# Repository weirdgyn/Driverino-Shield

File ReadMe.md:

# Driverino-Shield

### (italian noun) /ˈdraɪvərnəʊ/ : *little driver*

Driverino-Shield is a simple, low power, controller for [BLDC](https://en.wikipedia.org/wiki/Brushless_DC_electric_motor) sensored motors.
The aim of the project was to create an Arduino shield to drive PM BLDC motor(s) rated about 50-100W.
The board is designed around TI MCT8316Z BLDC chip: a very compact full featured driver that can be easily controlled from Arduino microcontroller.

PCB has been fully designed with KiCAD.

# TODO:

- [X] Submit to Made-With-KiCAD
- [ ] Add features:
   - [ ] encoder input.
   - [ ] current measurement (via INA250).
- [ ] Optimize PCB layout.
- [ ] Write Library.
   - [ ] Write Firmware.

# License

This project is released under CERN Open Hardware Licence Version 2 - Permissive.

# Links
* [This project on kitspace](https://kitspace.org/boards/github.com/weirdgyn/driverino-shield/)
* [TI MCT8316Z](https://www.ti.com/product/MCT8316Z?keyMatch=MCT8316Z&tisearch=search-everything)
* [Arduino](https://www.arduino.cc/)
* [KiCAD](https://www.kicad.org/)

#

Live long and prosper!

That's all folks.

By[t]e{s} Weirdgyn

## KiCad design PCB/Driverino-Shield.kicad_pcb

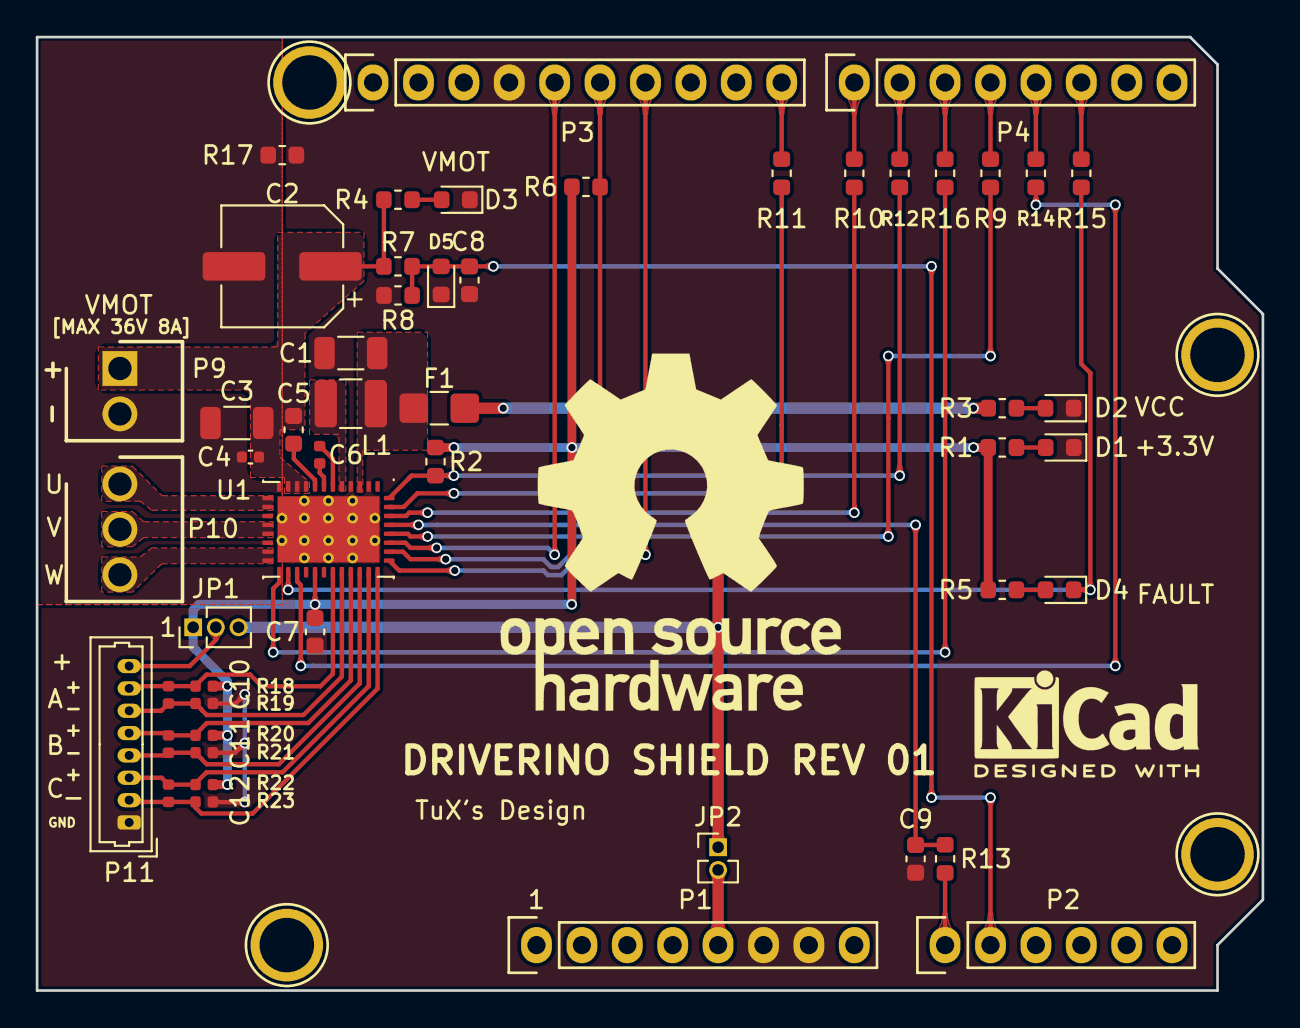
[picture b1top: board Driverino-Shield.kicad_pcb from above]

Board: 2 copper layers, 68.6 x 53.3 mm, 56 parts (0 on the bottom side), 47 nets.

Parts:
C1: 22uF; C_1206_3216Metric
C2: 150uF; CP_Elec_6.3x7.7
C3: 10uF; C_1206_3216Metric
C4, C10, C11, C12: 100nF; C_0402_1005Metric
C5, C7: 1uF; C_0603_1608Metric
C6: 10nF; C_0402_1005Metric
C8, C9: 100nF; C_0603_1608Metric
D1: ORANGE; LED_0603_1608Metric
D2, D4: BLUE; LED_0603_1608Metric
D3: GREEN; LED_0603_1608Metric
D5: Vz=5V; D_0603_1608Metric
F1: 200mA; Fuse_1206_3216Metric_Castellated
JP1: HAL_SEL; PinHeader_1x03_P1.27mm_Vertical
JP2: VCC_SEL; PinHeader_1x02_P1.27mm_Vertical
L1: 47uH; L_1210_3225Metric
P1: Power; Socket_Strip_Arduino_1x08
P2: Analog; Socket_Strip_Arduino_1x06
P3: Digital; Socket_Strip_Arduino_1x10
P4: Digital; Socket_Strip_Arduino_1x08
P5, P6, P7, P8: CONN_01X01; Arduino_1pin
P9: PWR; 39773-0002
P10: MOT; 39773-0003
P11: HALL; Molex_PicoBlade_53047-0810_1x08_P1.25mm_Vertical
R1, R3, R5, R7, R8, R13: 1k; R_0603_1608Metric
R2, R6: 5.1k; R_0603_1608Metric
R4: 4.7k; R_0603_1608Metric
R9, R10, R11, R12, R14, R15, R16, R17: 0R; R_0603_1608Metric
R18, R20, R22: 10k; R_0402_1005Metric
R19, R21, R23: 0R; R_0402_1005Metric
U1: MCT8316Z; QFN-40_EP_5x7_Pitch0.5mm

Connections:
+3.3V: C7.1, JP1.1, P1.4, R1.1, R2.1, R5.1, R6.1, R18.2, R20.2, R22.2, U1.25
+5V: JP2.2, P1.5
+36V: C2.1, C3.2, C4.2, C5.2, P9.1, R4.1, R7.2, U1.9, U1.10, U1.11
/2: P4.6, R15.1
/3(**): P4.5, R14.1
/4: P4.4, R9.1
/5(**): P4.3, R16.1
/6(**): P4.2, R12.1
/7: P4.1, R10.1
/8: P3.10, R11.1
/11(**/MOSI): P3.7, U1.34
/12(MISO): P3.6, R6.2, U1.33
/13(SCK): P3.5, U1.35
/A0: P2.1, R13.2
/A1: C8.2, D5.2, P2.2, R7.1, R8.1
/A4(SDA): P2.5, P3.2
/A5(SCL): P2.6, P3.1
/BRAKE: R10.2, U1.38
/CS: R9.2, U1.36
/DRVOFF: R16.2, U1.21
/FAULT: D4.1, R15.2, U1.22
/FB: C1.2, F1.2, L1.1, U1.3
/FGOUT: R2.2, R12.2, U1.40
/HAN: C10.1, P11.6, R19.1, U1.28
/HAP: C10.2, P11.7, R18.1, U1.27
/HBN: C11.1, P11.4, R21.1, U1.30
/HBP: C11.2, P11.5, R20.1, U1.29
/HCN: C12.1, P11.2, R23.1, U1.32
/HCP: C12.2, P11.3, R22.1, U1.31
/ILIM: C9.2, R13.1, U1.37
/PWM: R11.2, U1.39
/SLEEP: R14.2, U1.23
/SW: L1.2, U1.5
/U: P10.1, U1.13, U1.14
/V: P10.2, U1.16, U1.17
/W: P10.3, U1.19, U1.20
GND: C1.1, C7.2, C8.1, C9.1, D1.1, D2.1, D3.1, D5.1, P1.6, P1.7, P3.4, P11.1, R8.2, R17.2, R19.2, R21.2, R23.2, U1.2, U1.4, U1.41
GNDPWR: C2.2, C3.1, C4.1, P9.2, R17.1, U1.12, U1.15, U1.18
unnamed: C5.1, U1.8
unnamed: C6.1, U1.7
unnamed: C6.2, U1.6
unnamed: D1.2, R1.2
unnamed: D2.2, R3.2
unnamed: D3.2, R4.2
unnamed: D4.2, R5.2
unnamed: JP1.2, P11.8
VCC: F1.1, JP1.3, JP2.1, R3.1

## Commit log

2021-05-10 Routing completed
2021-05-10 Update gerbers
2021-05-10 .tsv file generated
2021-05-11 Add kitspace.yaml, rename gerber folder
2021-05-11 Update BOM
2021-05-11 BOM Update
2021-05-11 Updated .gitignore
2021-05-11 .gitignore update, made-with-kicad logo
2021-05-11 Updated BOM
2021-05-12 Fixed VMOT input resistance partition, update BOM
2021-05-12 Changed F1 footprint, BOM update
2021-05-12 Create LICENSE
2021-05-13 Update directory tree
2021-05-13 Add teardrops
2021-05-13 Update LICENSE
2021-05-13 Get rid of tab characters in BOM
2021-05-13 Update BOM
    Revert on .tsv

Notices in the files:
parts and their libraries:
Copyright 2016 Accelerated Designs. All rights reserved.
